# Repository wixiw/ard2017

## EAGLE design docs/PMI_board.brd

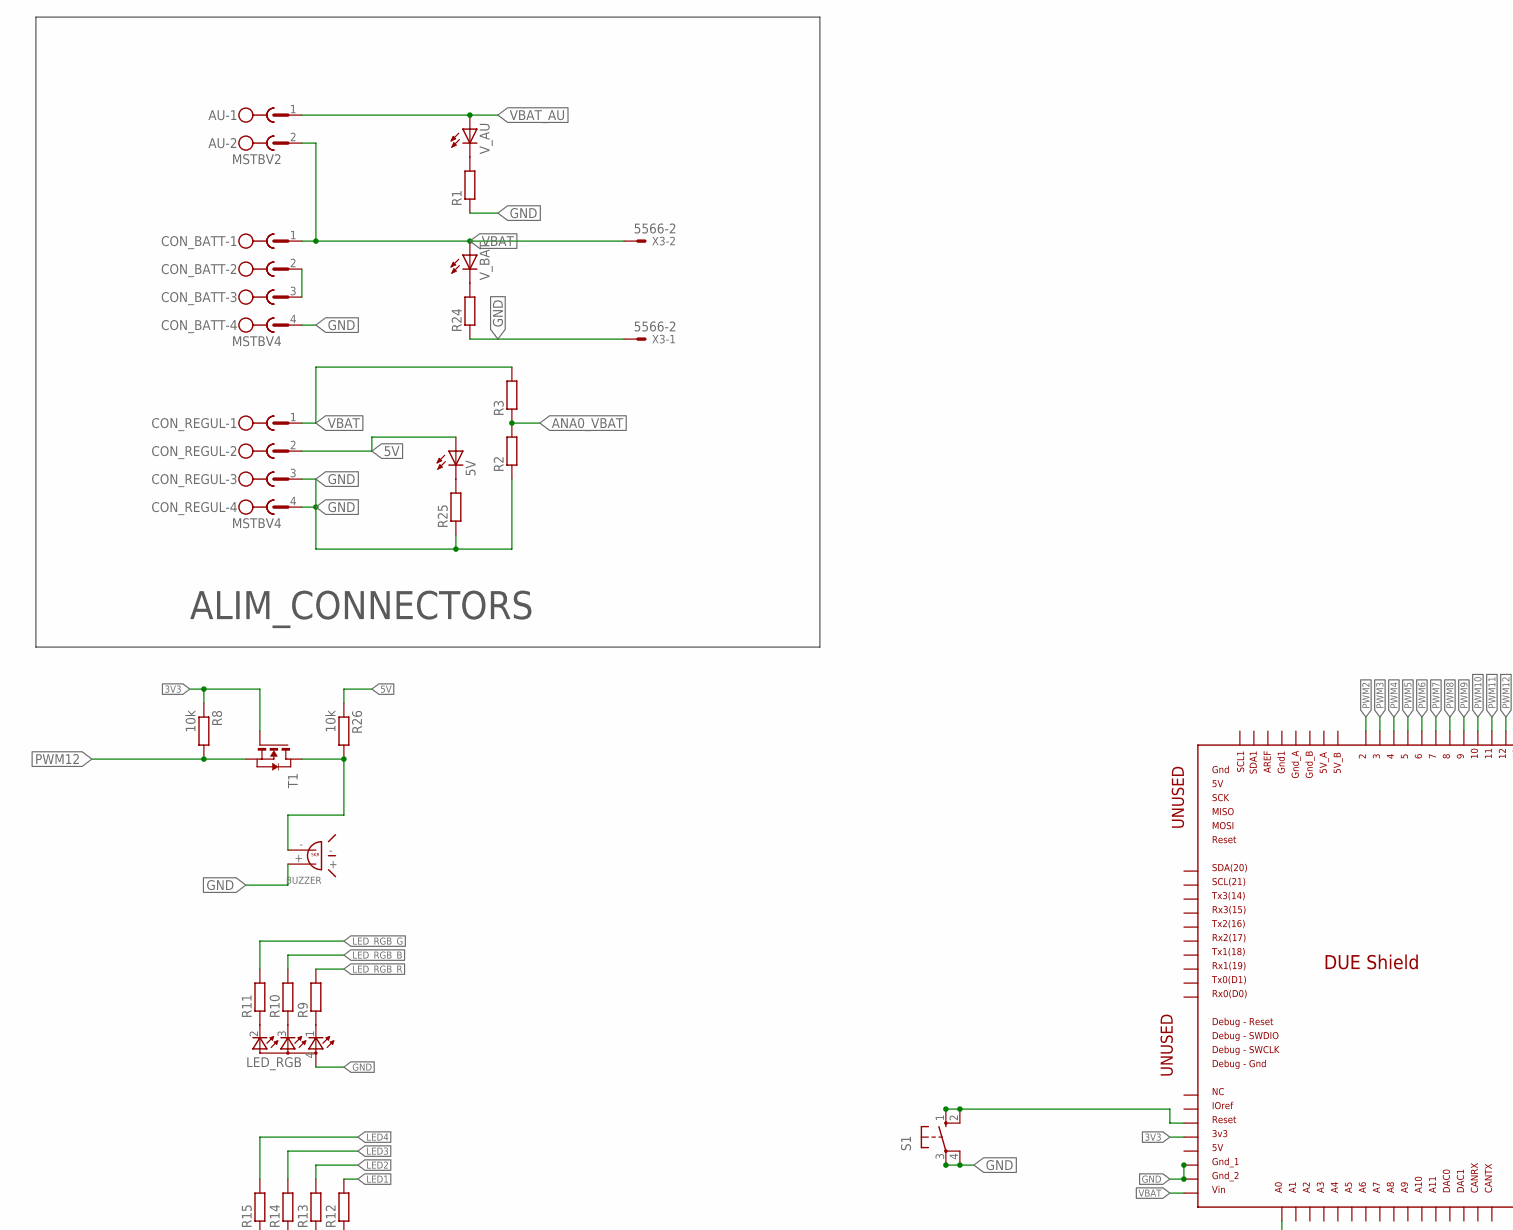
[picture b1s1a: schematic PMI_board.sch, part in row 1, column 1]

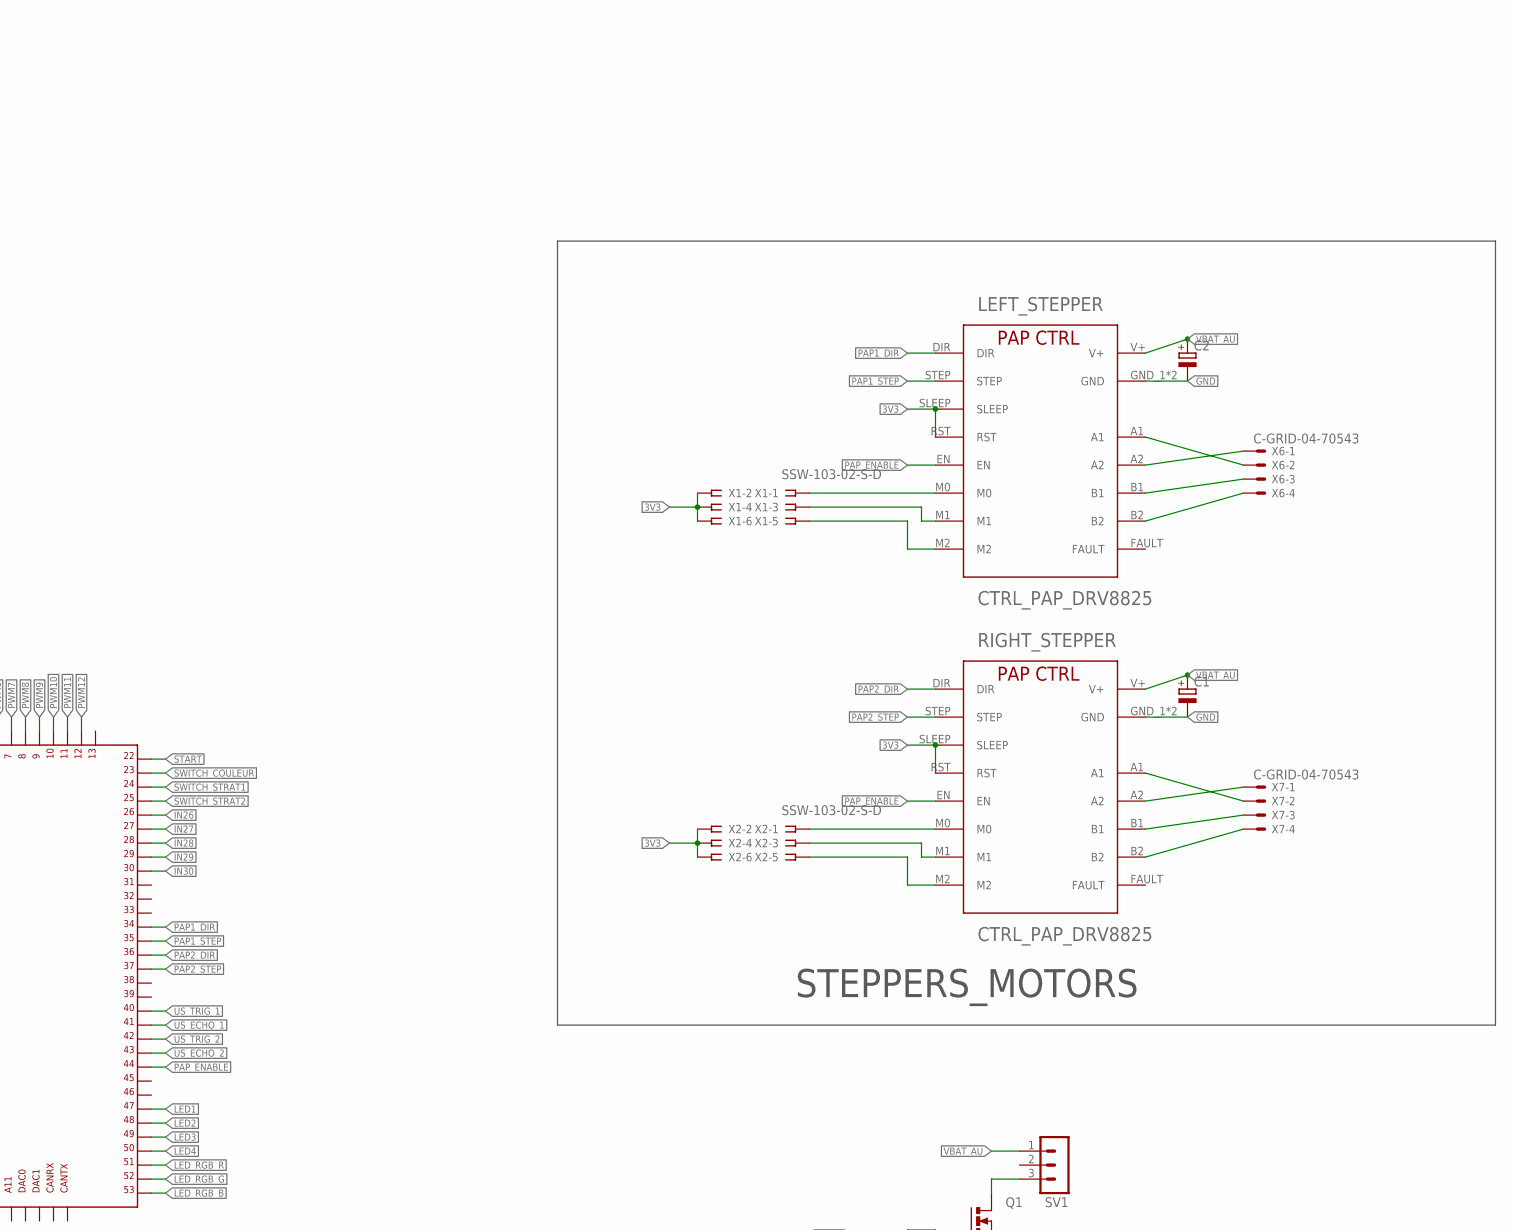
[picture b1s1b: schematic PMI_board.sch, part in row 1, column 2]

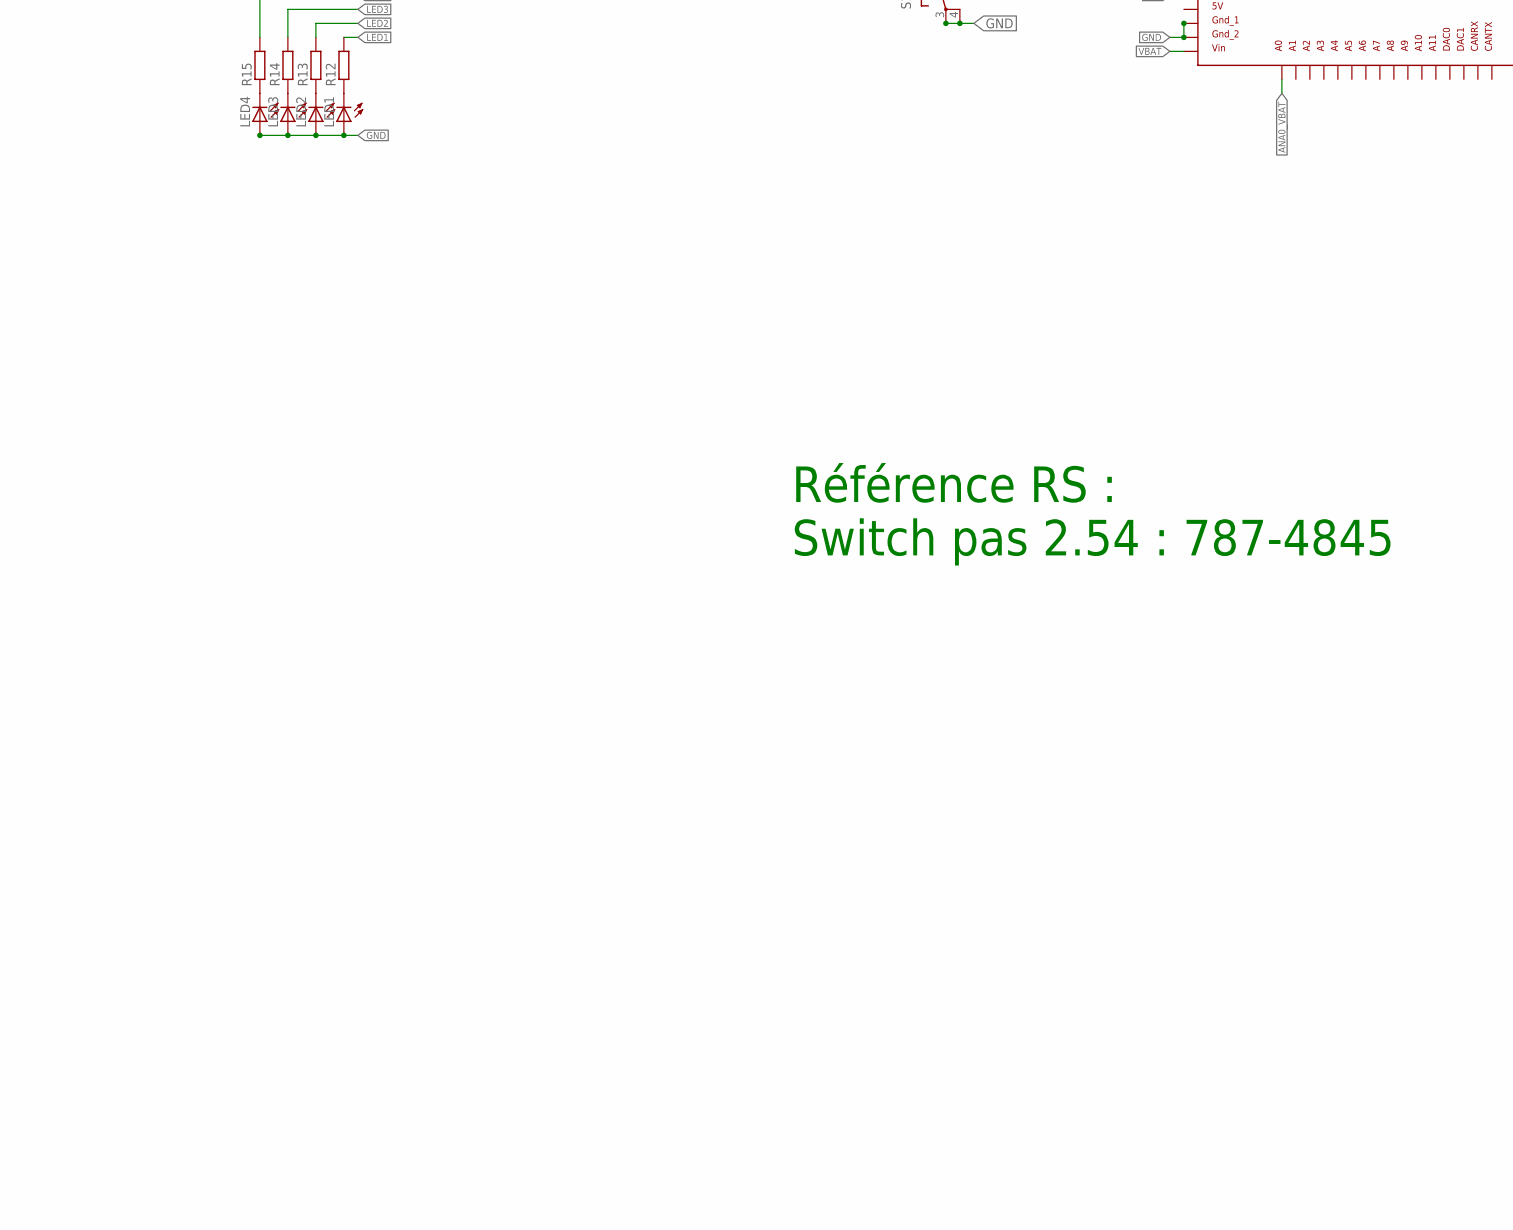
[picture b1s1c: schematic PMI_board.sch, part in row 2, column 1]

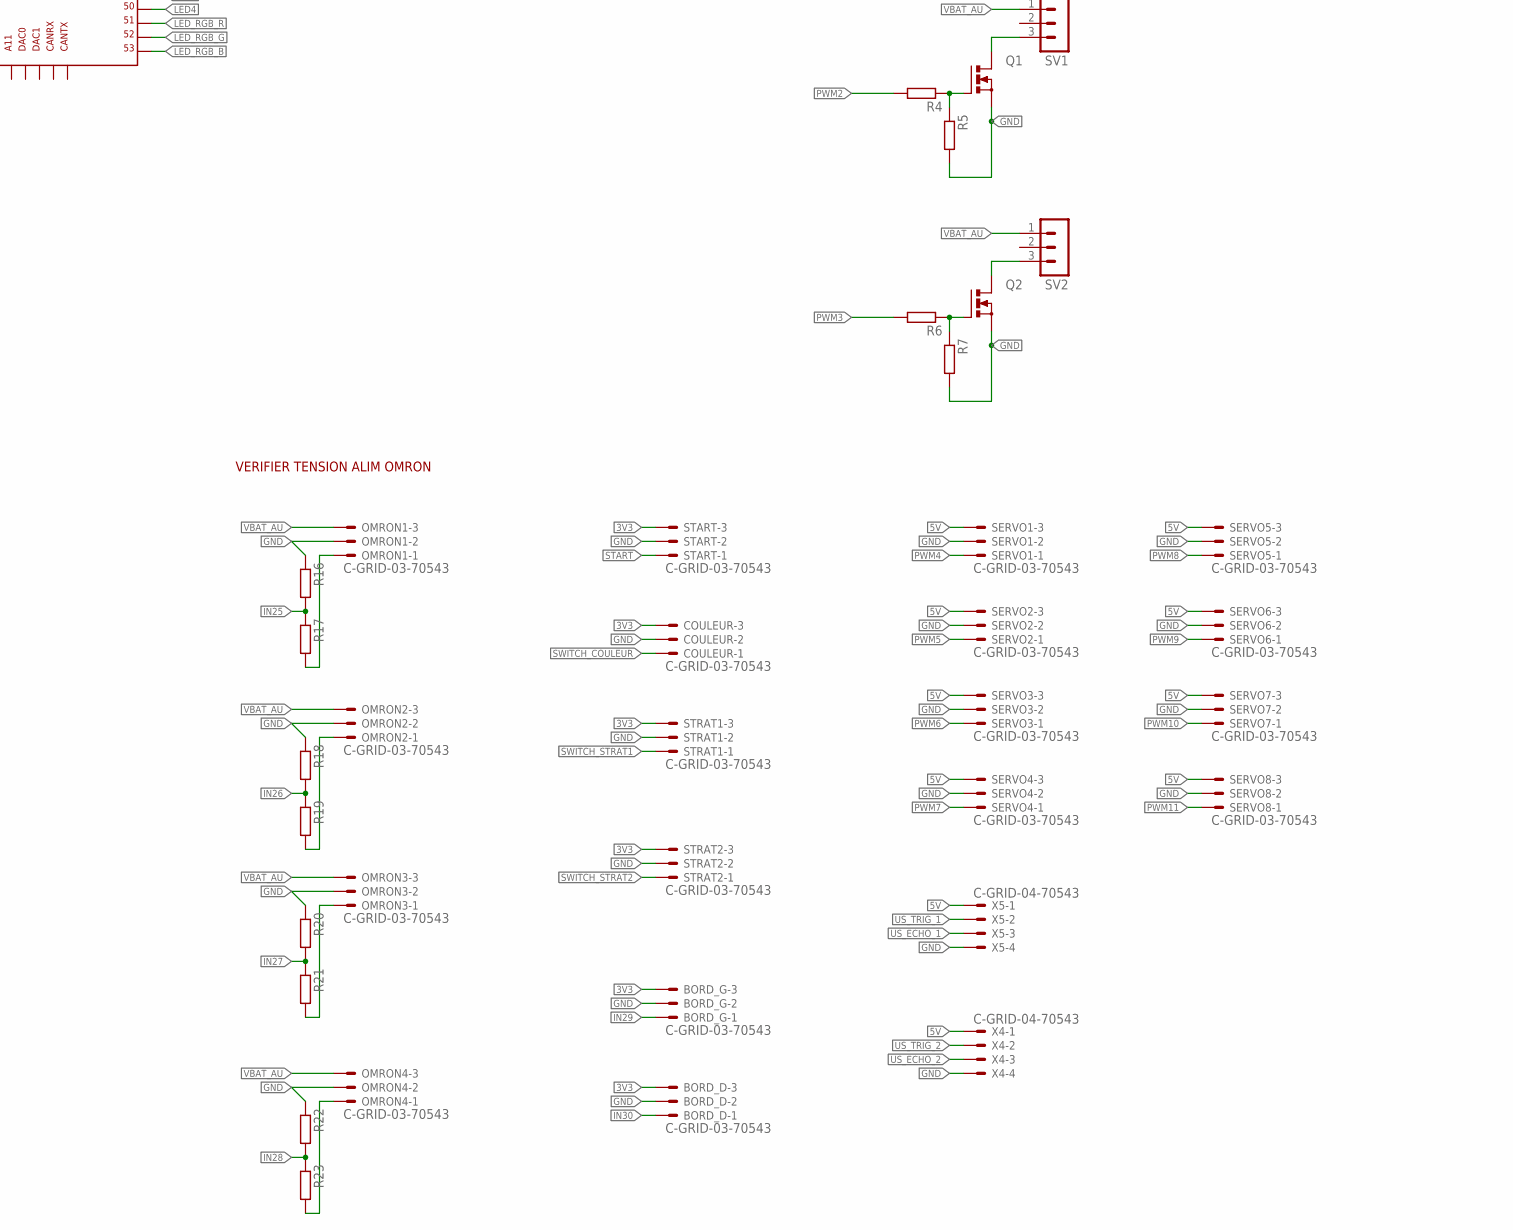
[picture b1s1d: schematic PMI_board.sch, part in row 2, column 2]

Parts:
5V: LED5MM
AU: MSTBV2
BORD_D: C-GRID-03-70543; 70543-03
BORD_G: C-GRID-03-70543; 70543-03
BUZZER: BUZZER
C1, C2: CPOL-EUD; PANASONIC_D
CON_BATT: MSTBV4
CON_REGUL: MSTBV4
COULEUR: C-GRID-03-70543; 70543-03
LED1, LED2, LED3, LED4: LED3MM
LED_RGB: TOPLED-3QPE_MAPPING; P-LCC-4-3
LEFT_STEPPER: CTRL_PAP_DRV8825; CTRL_PAP
OMRON1, OMRON2, OMRON3, OMRON4: C-GRID-03-70543; 70543-03
Q1, Q2: PMOSFET_NTO220BV; TO220BV
R1, R2, R3, R4, R5, R6, R7, R9, R10, R11, R12, R13, R14, R15, R16, R17, R18, R19, R20, R21, R22, R23, R24, R25: R-EU_M1206; M1206
R8, R26: 10k; M1206
RIGHT_STEPPER: CTRL_PAP_DRV8825; CTRL_PAP
S1: 10-XX; B3F-10XX
SERVO1, SERVO2, SERVO3, SERVO4, SERVO5, SERVO6, SERVO7, SERVO8: C-GRID-03-70543; 70543-03
START: C-GRID-03-70543; 70543-03
STRAT1, STRAT2: C-GRID-03-70543; 70543-03
SV1, SV2: MA03-1
T1: NMOSSOT23; SOT-23
U$1: DUE(NORMAL)
V_AU: LED5MM
V_BAT: LED5MM
X1, X2: SSW-103-02-S-D
X3: 5566-2
X4, X5, X6, X7: C-GRID-04-70543; 70543-04

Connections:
3V3: BORD_D.3, BORD_G.3, COULEUR.3, LEFT_STEPPER.RST, LEFT_STEPPER.SLEEP, R8.1, RIGHT_STEPPER.RST, RIGHT_STEPPER.SLEEP, START.3, STRAT1.3, STRAT2.3, T1.3 (G), U$1.3V3, X1.2, X1.4, X1.6, X2.2, X2.4, X2.6
5V: 5V.A, CON_REGUL.2, R26.1, SERVO1.3, SERVO2.3, SERVO3.3, SERVO4.3, SERVO5.3, SERVO6.3, SERVO7.3, SERVO8.3, X4.1, X5.1
A1: LEFT_STEPPER.A1, X6.2
A2: LEFT_STEPPER.A2, X6.1
ANA0_VBAT: R2.2, R3.1, U$1.A0
B1: LEFT_STEPPER.B1, X6.3
B2: LEFT_STEPPER.B2, X6.4
GND: BORD_D.2, BORD_G.2, BUZZER.+, C1.-, C2.-, CON_BATT.4, CON_REGUL.3, CON_REGUL.4, COULEUR.2, LED1.A, LED2.A, LED3.A, LED4.A, LED_RGB.4 (A2), LEFT_STEPPER.GND_1 (GND), LEFT_STEPPER.GND_2 (GND), OMRON1.2, OMRON2.2, OMRON3.2, OMRON4.2, Q1.S, Q2.S, R1.1, R2.1, R5.2, R7.2, R16.1, R18.1, R20.1, R22.1, R24.1, R25.1, RIGHT_STEPPER.GND_1 (GND), RIGHT_STEPPER.GND_2 (GND), S1.3, S1.4 (P1), SERVO1.2, SERVO2.2, SERVO3.2, SERVO4.2, SERVO5.2, SERVO6.2, SERVO7.2, SERVO8.2, START.2, STRAT1.2, STRAT2.2, U$1.GND_1, U$1.GND_2, X3.1, X4.4, X5.4
IN25: R16.2, R17.1
IN26: R18.2, R19.1, U$1.26
IN27: R20.2, R21.1, U$1.27
IN28: R22.2, R23.1, U$1.28
IN29: BORD_G.1, U$1.29
IN30: BORD_D.1, U$1.30
LED1: R12.2, U$1.47
LED2: R13.2, U$1.48
LED3: R14.2, U$1.49
LED4: R15.2, U$1.50
LED_RGB_B: R10.2, U$1.53
LED_RGB_G: R11.2, U$1.52
LED_RGB_R: R9.2, U$1.51
unnamed: CON_BATT.2, CON_BATT.3
unnamed: R1.2, V_AU.K (C)
unnamed: LEFT_STEPPER.M0, X1.1
unnamed: LEFT_STEPPER.M1, X1.3
unnamed: LEFT_STEPPER.M2, X1.5
unnamed: RIGHT_STEPPER.M0, X2.1
unnamed: RIGHT_STEPPER.M1, X2.3
unnamed: RIGHT_STEPPER.M2, X2.5
unnamed: S1.1 (S), S1.2 (S1), U$1.RESET
unnamed: Q1.G, R4.1, R5.1
unnamed: Q1.D, SV1.3
unnamed: Q2.G, R6.1, R7.1
unnamed: Q2.D, SV2.3
unnamed: BUZZER.-, R26.2, T1.1 (D)
unnamed: OMRON1.1, R17.2
unnamed: OMRON2.1, R19.2
unnamed: OMRON3.1, R21.2
unnamed: OMRON4.1, R23.2
unnamed: RIGHT_STEPPER.A1, X7.2
unnamed: RIGHT_STEPPER.A2, X7.1
unnamed: RIGHT_STEPPER.B1, X7.3
unnamed: RIGHT_STEPPER.B2, X7.4
unnamed: LED_RGB.1 (CRED), R9.1
unnamed: LED_RGB.3 (CBLUE), R10.1
unnamed: LED_RGB.2 (CGREEN), R11.1
unnamed: LED1.K (C), R12.1
unnamed: LED2.K (C), R13.1
unnamed: LED3.K (C), R14.1
unnamed: LED4.K (C), R15.1
unnamed: R24.2, V_BAT.K (C)
unnamed: 5V.K (C), R25.2
PAP1_DIR: LEFT_STEPPER.DIR, U$1.34
PAP1_STEP: LEFT_STEPPER.STEP, U$1.35
PAP2_DIR: RIGHT_STEPPER.DIR, U$1.36
PAP2_STEP: RIGHT_STEPPER.STEP, U$1.37
PAP_ENABLE: LEFT_STEPPER.EN, RIGHT_STEPPER.EN, U$1.44
PWM2: R4.2, U$1.2
PWM3: R6.2, U$1.3
PWM4: SERVO1.1, U$1.4
PWM5: SERVO2.1, U$1.5
PWM6: SERVO3.1, U$1.6
PWM7: SERVO4.1, U$1.7
PWM8: SERVO5.1, U$1.8
PWM9: SERVO6.1, U$1.9
PWM10: SERVO7.1, U$1.10
PWM11: SERVO8.1, U$1.11
PWM12: R8.2, T1.2 (S), U$1.12
START: START.1, U$1.22
SWITCH_COULEUR: COULEUR.1, U$1.23
SWITCH_STRAT1: STRAT1.1, U$1.24
SWITCH_STRAT2: STRAT2.1, U$1.25
US_ECHO_1: U$1.41, X5.3
US_ECHO_2: U$1.43, X4.3
US_TRIG_1: U$1.40, X5.2
US_TRIG_2: U$1.42, X4.2
VBAT: AU.2, CON_BATT.1, CON_REGUL.1, R3.2, U$1.VIN, V_BAT.A, X3.2
VBAT_AU: AU.1, C1.+, C2.+, LEFT_STEPPER.V+, OMRON1.3, OMRON2.3, OMRON3.3, OMRON4.3, RIGHT_STEPPER.V+, SV1.1, SV2.1, V_AU.A

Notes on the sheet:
ALIM_CONNECTORS
STEPPERS_MOTORS
VERIFIER TENSION ALIM OMRON
Référence RS : Switch pas 2.54 : 787-4845

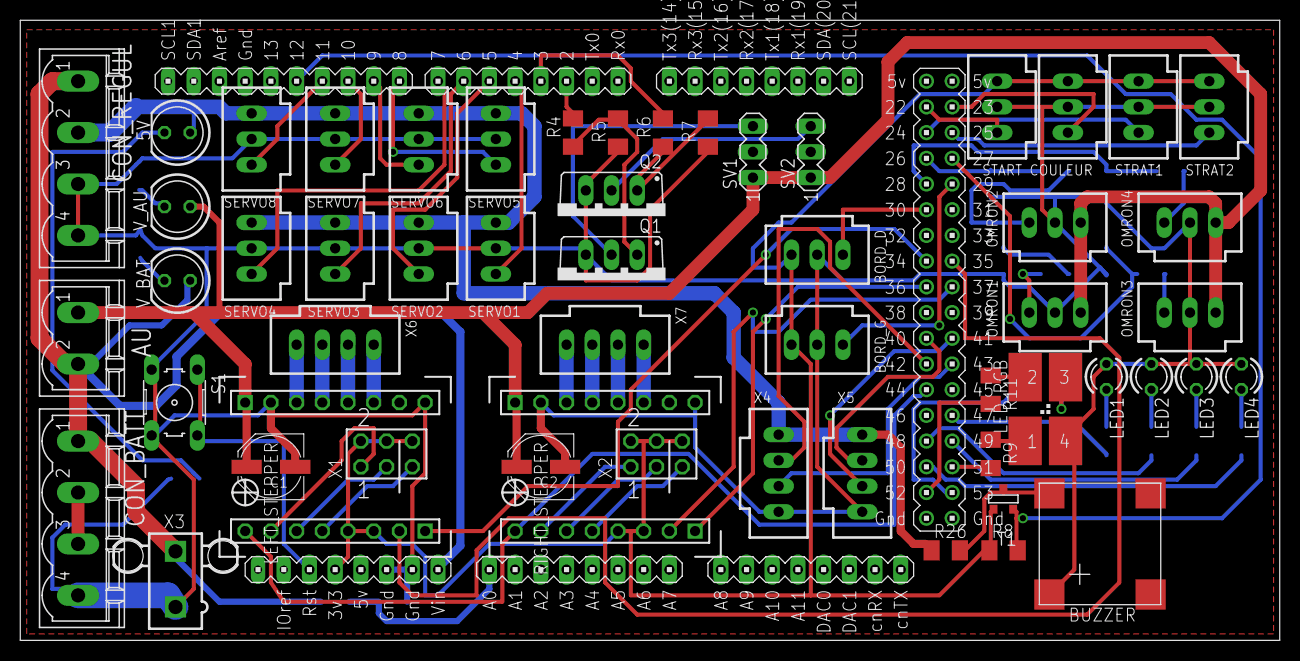
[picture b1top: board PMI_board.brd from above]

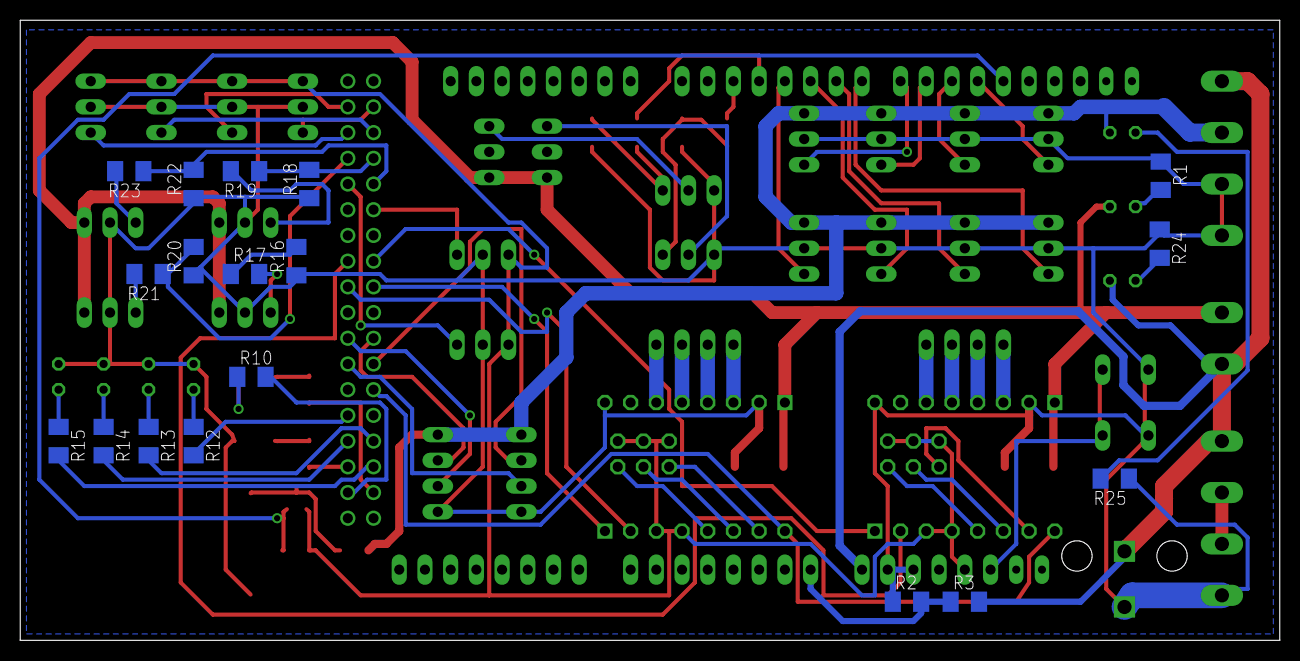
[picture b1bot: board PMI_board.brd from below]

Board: 2 copper layers, 124.4 x 61.3 mm, 74 parts (18 on the bottom side), 78 nets.

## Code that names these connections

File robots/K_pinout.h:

#ifndef PINOUT_H
#define PINOUT_H

#include <variant.h>

#define MOSFET1         2
#define MOSFET2         3
#define SERVO1          4
#define SERVO2          5
#define SERVO3          6
#define SERVO4          7
#define SERVO5          8
#define SERVO6          9
#define SERVO7          10
#define SERVO8          11
#define BUZZER          12
#define LED_DUE_L       13
#define BUTTON_START    22
#define BUTTON_COLOR    23
#define BUTTON_USER1    24
#define BUTTON_USER2    25
#define OMRON1          31
#define OMRON2          26
#define OMRON3          27
#define OMRON4          28
#define BORDURE_G       29
#define BORDURE_D       30
#define CS_SDCARD	31  //not mapped to child card
#define PAPG_DIR        34  // Gauche = PAP1
#define PAPG_STEP       35
#define PAPD_DIR        36  // Droite = PAP2
#define PAPD_STEP       37
#define US_TRIG_1       40
#define US_ECHO_1       41
#define US_TRIG_2       42
#define US_ECHO_2       43
#define PAP_ENABLE      44
#define LED1            47
#define LED2            48
#define LED3            49
#define LED4            50
#define LED_RGB_R       51
#define LED_RGB_G       52
#define LED_RGB_B       53
#define LED_DUE_RX	72
#define LED_DUE_TX	73

#define ANA0_VBAT       A0

#endif

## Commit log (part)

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2016-10-19 :space_invader: Added .gitattributes & .gitignore files
2016-10-19 FreeRtos setup + arp_slave backports
2016-10-21 HMI thread added, Teleop thread added, ArdOs statistics added
2016-11-09 WIP Navigation introduction
2016-11-10 Mutex fixed (lock/unlock was inverted...) Log Thread safety fixed. Navigation added in the actuator thread.
2016-11-21 Timer tested ok (unit test added) Buttons working (tested on PMI) Omron working (tested on PMI, SDcard was on Omron1=> fixed) Navigation testable on PMI
2016-11-23 Doc updated with USB-prog integration with Atmel (via bossac)
2016-11-30 Switch to Atml Studio build system
2016-11-30 ignore config updated to prevent unexpected files to return to the repo
2016-12-02 Boot ok
    Les flags de compilations -Os ont été remis, sans ça, ça ne boote pas et
    ça fait une hard fault.
    Ménage dans les fichiers de link non utilisé pour prémunir des accidents
    Correction de l'assert du à un signal non initialisé dans gpio tools (à
    cause d'une typo)
2016-12-06 Correction bug wait à l'infini quand carte SD absente
2016-12-09 Isofonctionnel 2016
    descente timeout carte SD
    Correction strat blocantes
    ajout dieMotherfucker
    ajout stop navigation.
    mise à jour document d'architecture (Navigation repassée dans RSP)
    ajout d'un mini thread pour jouer avec les actionneurs
2016-12-13 Towards simulation as "real + teleop".
    TeleopThread moved to AL.
    Start simulation POC.
    HMI is hidden inside Robot2017 which acts as a real decorator now.
    External code added : nanopb in order to serealize messages.
2016-12-16 Way to simulation
    Folder filtering in eclipse configure for quicker search
    C++11 syntax propagated (for, auto)
    Event system added to be able to emulate a "select()"
    HMI interface masked behing Robot2017 decorator
    Teleop thread improved to be able to send configure/start event to boot
    without HMI interaction
2017-01-04 Communication layer improved with HDLC and protobuf introduction. Vizu started
2017-01-06 HDLC moved to another library, with a python binding. Vizu is sending HDLC messages properly. Robot is not decoding
2017-01-06 Le robot reçoit et décode les trames HDLC
2017-01-07 Revert "Protobuf layer added for Teleop. Vizu is now capable to start a match"
    This reverts commit a96aee9cbbc2652be03fdd017afed8d220c9c95c.
2017-01-07 ignore files
2017-01-08 Python modules load all files automatically, setPos,goto request implemented, Nav completely broken
2017-01-10 Protobuf issue on log fixed.
2017-01-14 Working color sensor, correct pull request comments
2017-01-14 Add Color Sensor module. For now, not working if the sensor is connected. (#1)
    * Add Color Sensor module. For now, not working if the sensor is connected.
    * Working color sensor, correct pull request comments
2017-01-17 OS Refactor, logging Thread added to logs, Logs Filters, libc init fixed
2017-01-20 clean com stack setup (emb +vizu), OS can log, Assert prints, Telemetry gathering and msg added,
2017-01-22 Telemetry poller, Filtered input inversion, python maths re-use
    FilteredInput can now be inverted => omron configured to use the
    feature. Telemetry poller thread added in vizu. Legacy maths python code
    reused
2017-01-23 Robot drawing added to Vizu. Associated bugfixes
2017-02-06 Reboot cmd added, OS debugged, Unit test maintained, Shortcuts added in vizu
    There were some race condition with initialization order and destruction
    of some variables initialized in the main() stack which is destructed
    afterward.
    Vizu polling accelerated.
    Angle normalization management improved (C++ and python).
    Com tab buttons not related to communication moved to Robot tab
2017-02-07 Add Color sensor to telemetry
2017-02-07 Master (#2)
    Add Color Sensor module with basic algorithm to detect yellow and blue. Integration with telemetry and Vizu.
2017-02-13 Com testing : max length messages + all characters tested (+fixes)
2017-02-27 Some non critical WIP, it may break the master branch
2017-03-06 Partial commit (may break build) com library isolated, Unit test maintenance, interrupts priorities in Robot2017
2017-03-07 Bug in hdlc fixed (send buffer overflow), Memory leak in OS stats fixed, stack total stat added.
2017-03-09 Navigation debug in progress : CPU overrun fixed, moves are displayed properly in Vizu. Orders are still bugged.
2017-03-15 Ajout procédure installation faite lors de l'installation du PC de Tanguy
2017-03-16 SW Cleaning (see k#104) : unused code deleted, Uart driver isolated, Strings isolated, SW Architecture conformity
2017-03-20 Build fixed + tests buzzers
2017-03-21 Add bossac to repo
2017-03-21 Ajout installation arduino
2017-03-22 Vizu can now request buzzer sound to robot. Help tab added
2017-03-26 Buzzer fixed, Imperial march added and tested ok.
2017-03-27 Debug anti-collision OK, Update AccelStepper
2017-03-29 Vizu improved to automatically generates shortcut help
2017-04-02 Vizu shortcuts/tabs availability improved
2017-04-03 #153 Add Serial Communication stats
2017-04-03 update gitignore files
2017-04-03 Vmax is no more a configuration, it's computed from stop distance.
2017-04-04 Adding protobuf files in com generator
2017-04-04 Docs moved to SVN
2017-04-04 Correction merge foireux de willy
2017-04-06 Robot configuration check added. Nav.setSpeedAcc check added. Vizu : tab Robot reworked to prepare Sensors landing
2017-04-06 Ajout feedback HMI dans telemetry. Ajout onglet Status bas niveaux
2017-04-09 New BSP wiring. TabRobot with a new tab for servo commands
2017-04-11 Strat 0, correction IHM vizu onglet Help
2017-04-12 k#203 : Intégration des plans méca table/robot en SW
    Robot config reworked to add introduce Params/Configs.
    Mutex added in RemoterControl emission API.
    Robot and vizu now manages the 2 robots binaries
    Robot navigation command crash fixed.
    Robot and table plan added to help tab
2017-04-14 Strat framework
    Ajout modèle donnée strat
    Ajout dessin cylindres dans Vizu
    Gestion disparition des items
    Correction crash onglet config
    Introduction des LSA
    Correction erreur unité angle PointCap
2017-04-16 Vizy exit behavior improved (a lot!), default sub-tab selection are now persisted to be restored on next execution
2017-04-16 Strategy color/start buttons added into Vizu tab (and removed from Robot.Cmd tab)
2017-04-17 Servo IT priority configure to prevent shaking. Servo lib reworked for better IT efficiency. USB upload fixed. Measure on all IT.
2017-04-18 Creation of arm and lifter state machines. Integration in ActuatorsThread
2017-04-18 Add Chrono to count the match time
2017-04-20 Strat runtime changed from events to periodic. Lifecycle tested to manage end of match.
2017-04-22 Workaround uncontrollable servo from vizu
2017-04-22 Yakindu integration is now compatible with previous strategies
2017-04-22 Navigation logs fixes
2017-04-24 Strat APIintegration
    Servo cmd range changed (180=>1000),
    PolledObject init bug corrected.
    End match power off management
    Actuators machines now correctly manage their output before being
    activated
    Strat API created for states machines
2017-04-25 Nouvelle strat Tanguy (WIP) & refactoring nommage elements de table
2017-04-26 Strat 0 au propre, avec recalages
2017-04-26 DAT strat commit : strat layer rework to correct architectures/depencendies issues. Should be ready for diffusion
2017-04-27 Calibration PEN
2017-04-27 commande servo par défaut à 500 (la moitié)
2017-04-29 common LSA skeletons added
2017-04-29 AccelServo added. Strategy API improved with all sensors.
2017-04-29 Update to manage several python verions installation
2017-04-30 Atmel solution fix to prevent a crash on wix dell pc
2017-05-02 FSM dedicated to a robot moved to its robot folder to reduce binary size. First complete strategy in FSM/LSA
2017-05-02 Recal bugfix, Homol Pen start up
2017-05-04 Strat/LSA Failure return code available. Lifecycle reworked. Selftest and Install procedure for Pen.
2017-05-05 Color symetrization management improved and bugfixes
2017-05-05 Simulation awarness, Cylinder stock color awarness, Tration strategy improved
2017-05-07 var readonly tags in FSM replaced by const to fit user guide. Some generated files were erronously commited => deleted
2017-05-08 Motion orders timeout added. Log debug can be activated dynamically. Ghost logs cleaned
2017-05-09 Omron gathered, Opponent detection extracted from navigation. Opponent detection table filter added
2017-05-09 LSA timeout added.
2017-05-12 Graph based motion introduction
2017-05-13 Trying to survive
2017-05-13 Navigation follows the graph in GotoGraph (expect first point)
2017-05-13 Goto Graph ok sans les caps
2017-05-13 GraphTo fonctionne avec les caps en marche AV, mais plante à la fin de l'ordre
2017-05-14 Ajout des points symétriques, fin de dev
2017-05-15 Bip WAF config, Vizu recal on border added to commands
2017-05-15 inversion du signal des switch de recalage
2017-05-17 Tration repaired. Recal regression with front switches inversion repaired
2017-05-17 Cleaning pass 2
2017-05-18 Demonstration for BA on small table + dispenser
2017-05-19 Pen calibration, Recal in 2 steps, Speed limitation from actuators WIP,
2017-05-20 Better max speed management, speed reduced when actuators are out, servo position getter fixed, Recal from vizu has a dropdown menu
2017-05-20 Display color during color manipulation before validating
2017-05-20 Kinematics reduced:prevent curved trajectories, Vizu robustness to disconnection greatly improved, Robot set its start position before match
2017-05-20 Calibration tab improved
2017-05-20 HMI hearbeat LED is now started after color configuration
2017-05-21 Installation procedure ready
2017-05-21 Motion power disabled when not used. Lifter FSM implemented for lifting. New tab in Vizu to drive the lifter
2017-05-21 Lifter error case management
2017-05-22 FSM arms in progress
2017-05-22 Rotator integration in BSP/RSP/Vizu. Funny action preparation, Recals witches disabled, Simu verificated
2017-05-22 missing file
2017-05-22 Configure strat to match hardware
2017-05-22 Bugfix in selftest symetrisation
2017-05-22 LSA has now a parameter to configure something (like the number of withdrawned cylinders
2017-05-22 Recal position added on rounded borders. Recal retry introduced. Rear recal switch disabled
2017-05-23 missing files
2017-05-23 Configure arms with switch limit
2017-05-23 Rework of dispenser state machine with arm state machine.
    Conflicts:
    robot/Common/2_AL/2_LSA/FSM_LSA_Dispenser.sct
    robot/Common/2_AL/2_LSA/FSM_LSA_GetCylinder_B.sct
    robot/Common/2_AL/2_LSA/FSM_LSA_GetCylinder_C.sct
    robot/Common/2_AL/2_LSA/FSM_LSA_PooBorderOpp.sct
    robot/Common/2_AL/2_LSA/FSM_LSA_PooBorderOwn.sct
2017-05-23 Integration fixes
2017-05-23 Actuators API rework, E cylinder catch adjusted
2017-05-23 Le code pour protobuf c'est dans le proto pas dans le code généré ... Bizuth !
2017-05-23 Correct mapping
2017-05-23 Correct servo control 7 and 8
2017-05-24 Lifter and Arm FSM robustness improved. Vizu updated accordingly. Avoidance activation fix. RC for homologation
2017-05-24 Homol RC2
2017-05-24 Reprise zone aveugle + ajout dispensers + ajustement des bras au selftest pour position fliflop correcte, correctiond es mutex temps
2017-05-25 Correct lifter ready
2017-05-25 Amélioration Get C/GetB
2017-05-25 Simulation check moved from TabCom to TabStrat, Yellow selected by default, Navigation recal switch mangmt improved (include rounded border)
2017-05-25 Polish on GetB
2017-05-25 revert shit
2017-05-25 STrat tration for 1st match
2017-05-25 Recal bugfix on border + start sequence, Arm init position changed to prevent conflicts, Tration rush ok, Arm taken flag ack
2017-05-25 Modif recalage en Y Start area TRATION
2017-05-25 Lifter doesn't lift cylinder 5
2017-05-25 Bug fix symetrie turnTo
2017-05-25 Bugfix timeout turnDelta trop petit pour les petits angles
2017-05-25 Ajustement dispenser pour gestion Tration
2017-05-25 correct shit (you must write speed limite before asking an order)
2017-05-26 Ajout recalXXXSpecial + rouleau aux API de FSM (manque FSM_GetB à faire chez Tanguy)
2017-05-26 Suppression GetB/ GetC de Pen
2017-05-26 Calib après changement rouleau
2017-05-26 Correction transition Get_C
2017-05-26 Ajustement vitesse marche avant + ajustement GetC et Dispenser
2017-05-26 Tration pour match 3
2017-05-26 Change entry point of chiage zone
2017-05-26 3rd match for pen
2017-05-26 Amélioration robustesse bras (en tenant compte des évols lifter)
2017-05-26 Gestion cas rouler sur cylindre
2017-05-26 match 4
2017-05-26 Commit pour Tanguy
2017-05-26 Mise au point rushs tration + gestions conflits bras/ascenseurs
2017-05-26 Tentative Yolo
2017-05-26 Réglage définitif rouleau
2017-05-27 Get B and poo Border 5
